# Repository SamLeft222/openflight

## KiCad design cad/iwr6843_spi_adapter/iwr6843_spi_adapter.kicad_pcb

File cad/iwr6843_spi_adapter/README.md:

# IWR6843LEVM → Raspberry Pi 5 SPI adapter

Small 2-layer board (34.0 × 25.9 mm) that plugs into the IWR6843LEVM's 60-pin
**J1** (MMWAVEICBOOST) connector and brings the radar's SPI-A port out to a
0.1" header for jumper wires to the Pi 5. The goal is to move the ~733 KB
wide-profile dump over SPI (~0.6 s at 10 MHz) instead of the ~1 Mbaud CP2105
UART (~7 s).

> **Status: rev A, not yet built or tested.** ERC, DRC and schematic–PCB
> parity pass. The firmware SPI path and Pi driver do not exist yet.

## What's on the board

| Ref | Part | Job |
|---|---|---|
| J1 | Samtec **QTH-030-01-L-D-A** (bottom side) | Mates the LEVM's J1 (QSH-030-01-L-D-A), 5.00 mm stack |
| J2 | 1×11 2.54 mm header (top side) | Jumpers to the Pi 5 |
| U1, U2 | SN74LVC2G34DBVR, powered by **radar 3V3** | Pi → radar: SCLK, MOSI, CS (U2 ch1 spare, input grounded) |
| U3 | SN74LVC2G34DBVR, powered by **Pi 3V3** | Radar → Pi: MISO, HOST_INTR |
| R1 | 100k to radar 3V3 | CS inactive (high) while the Pi pin is floating |
| R2–R5 | 100k to GND | No floating buffer inputs (SCLK, MOSI, MISO, INTR) |
| R6, R7 | 33 Ω | Damp ringing on the INTR/MISO jumpers |
| C1–C3 | 100 nF | Buffer decoupling (C3 is on the bottom) |

**Why buffers:** the IWR6843's digital I/O is not failsafe (TI SWRU585: do not
drive the pins without VIO present). The LVC2G34 has Ioff partial-power-down
(≤10 µA leakage at VCC = 0), so whichever side loses power, its buffer goes
inert and nothing back-feeds the unpowered chip.

## Before ordering (can't be checked in software)

1. **Mating orientation.** The footprint assumes QTH pin *n* mates LEVM J1
   (QSH) pin *n*, with the −A alignment pins on the row-01 side (per the
   Samtec land pattern). Print `fab/gerbers/*B_Cu*` at 1:1, or check a
   Samtec mated-pair drawing, and confirm pin 1 against the LEVM's J1
   silkscreen.
2. **Clearance behind the LEVM.** The adapter sits 5 mm under the LEVM's
   bottom side. The only bottom-side parts are J1, C3 (0.9 mm) and **J2's
   pin tails, which must be trimmed flush (≤1 mm)** so they can't touch the
   LEVM's bottom components (J6 is nearby).

## Ordering and assembly (PCBWay turnkey)

Run `./export_fab.sh` (regenerates, runs ERC/DRC, and exports into `fab/`):

| Upload | File |
|---|---|
| Gerbers + drills | `fab/iwr6843_spi_adapter-gerbers.zip` |
| BOM (PCBWay columns, MPNs) | `fab/pcbway_bom.csv` |
| Centroid / CPL | `fab/pcbway_cpl.csv` (origin = board lower-left, J2 excluded) |
| Assembly drawings | `fab/assembly/assembly_top.pdf`, `fab/assembly/assembly_bottom_mirrored.pdf` |

PCB options: 2 layers, FR-4, 1.6 mm, 1 oz, **ENIG** (flat pads for the
0.5 mm-pitch J1; HASL is too uneven), min track/spacing 5/5 mil, min hole
0.3 mm, tented vias, any mask colour.

Assembly: turnkey, **both sides** (J1 and C3 on the bottom, the rest on top).
J2 is not in the BOM or CPL. Solder it yourself and trim the tails flush.
Notes to include with the order:

> J1 (Samtec QTH-030-01-L-D-A) is on the BOTTOM side; its -A alignment pins go
> into the two 1.02 mm NPTH holes; pin 1 is marked on the bottom assembly
> drawing. U1-U3 pin 1 per the silkscreen dot. J2 (1x11 header) is NOT
> assembled. Please send placement confirmation images before production.

## LEVM setup

* Set switch **S1.4 OFF**. This routes SPI-A through the on-board TS3A5018
  mux to J1 instead of the CAN transceivers (PROC116A sheet 13). OpenFlight
  does not use CAN. TI's "functional mode" table leaves S1.4 ON; that is
  the only change.
* Keep powering the LEVM over USB as today. Do not connect J1 pin 2 (5V).

## Pi 5 wiring (jumpers ≤15 cm, cable-tie each signal to its GND)

| Adapter J2 | Signal | Pi 5 pin |
|---|---|---|
| 1 | 3V3 (powers U3) | 1 |
| 2, 4, 6, 8, 10 | GND | 6, 9, 14, 20, 25 |
| 3 | HOST_INTR (data ready) | 22 (GPIO25) |
| 5 | MISO | 21 (GPIO9) |
| 7 | MOSI | 19 (GPIO10) |
| 9 | SCLK | 23 (GPIO11) |
| 11 | CS | 24 (GPIO8 / CE0) |

None of these clash with the OPS243 UART wiring (Pi pins 2/4, 6, 8, 10, 11).
Enable SPI with `dtparam=spi=on`. Start at ≤10 MHz on jumpers.

## First power-up checks

1. Adapter only, unplugged from the LEVM: continuity between J2 even pins and
   J1 GND. No short between Pi 3V3, radar 3V3 and GND.
2. Plugged in, **everything off**: beep from J1-side nets to the LEVM's 0 Ω
   links: CS → R7, SCLK → R9, MOSI → R11, MISO → R12, INTR → R10
   (PROC116A sheet 8). This confirms the mating orientation.
3. Power the LEVM only: radar 3V3 is present at C1/C2 and U3 stays unpowered.
   Then the Pi only, then both.

## Sources

| Fact | Source |
|---|---|
| J1 pins 19/21/23/25 = SPI CS/CLK/MOSI/MISO, 16 = HOST_INTR, 4/6 = 3V3, even 20–50 = GND | TI PROC116A schematic, sheets 5, 8, 13 |
| VIOIN = 3.3 V, SPI-A behind TS3A5018, S1.4 selects SPI/CAN | PROC116A sheets 5 and 13; SWRU585 table 5-1 |
| J1 = QSH-030-01-L-D-A | PROC116A BOM |
| QTH land pattern, 5.00 mm mated height | Samtec QTH footprint Rev D, QTH print table 1 |
| LVC2G34 pinout, Ioff, DBV0006A land pattern | TI SN74LVC2G34 datasheet |

## Regenerating

Everything is generated from `generate.py` (schematic, footprints, project)
and `build_pcb.py` (placement, routing, pours). `NETS`/`PARTS` are the single
source of truth for both. Edit those, never the KiCad files.

```bash
K=/Applications/KiCad/KiCad.app/Contents
$K/Frameworks/Python.framework/Versions/Current/bin/python3 generate.py
$K/MacOS/kicad-cli sch erc --severity-all iwr6843_spi_adapter.kicad_sch
$K/MacOS/kicad-cli pcb drc --schematic-parity --refill-zones --severity-all iwr6843_spi_adapter.kicad_pcb
```

Expect only `lib_symbol_issues` / `lib_footprint_issues` warnings if your
KiCad has no global library tables configured. They are environment notices,
not design errors.

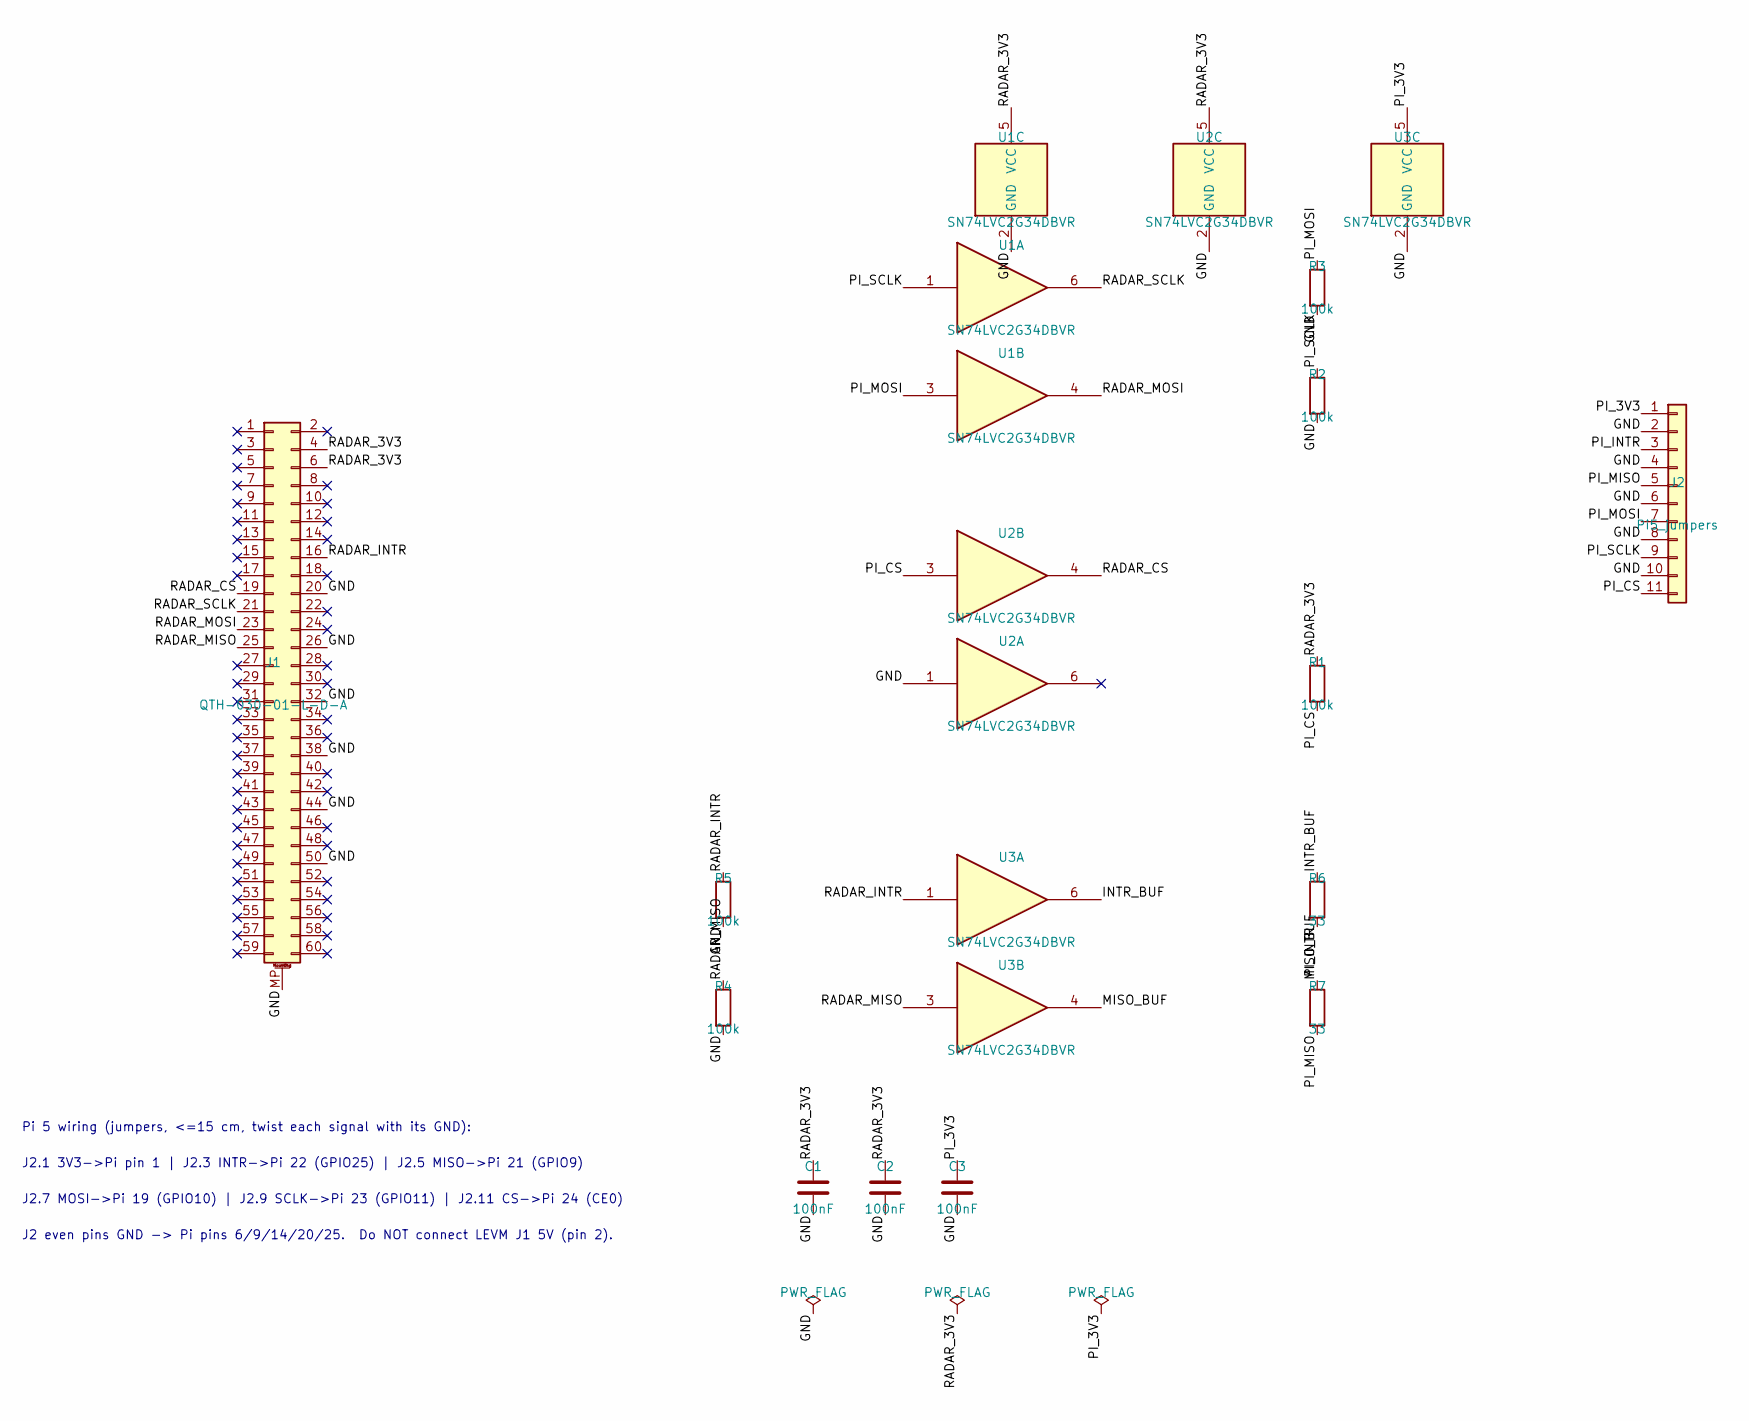
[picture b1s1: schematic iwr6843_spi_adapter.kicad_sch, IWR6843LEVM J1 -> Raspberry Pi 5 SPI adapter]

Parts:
C1, C2, C3: 100nF; C_0603_1608Metric; MPN CL10B104KB8NNNC
J1: QTH-030-01-L-D-A; Samtec_QTH-030-01-L-D-A; MPN QTH-030-01-L-D-A
J2: Pi5_jumpers; PinHeader_1x11_P2.54mm_Vertical
R1, R2, R3, R4, R5: 100k; R_0603_1608Metric; MPN RC0603FR-07100KL
R6, R7: 33; R_0603_1608Metric; MPN RC0603FR-0733RL
U1, U2, U3: SN74LVC2G34DBVR; TI_DBV0006A; MPN SN74LVC2G34DBVR

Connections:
/GND: C1.2, C2.2, C3.2, J1.20, J1.26, J1.32, J1.38, J1.44, J1.50, J1.MP (MountPin), J2.2, J2.4, J2.6, J2.8, J2.10, R2.2, R3.2, R4.2, R5.2, U1.2 (GND), U2.1, U2.2 (GND), U3.2 (GND)
/INTR_BUF: R6.1, U3.6
/MISO_BUF: R7.1, U3.4
/PI_3V3: C3.1, J2.1, U3.5 (VCC)
/PI_CS: J2.11, R1.2, U2.3
/PI_INTR: J2.3, R6.2
/PI_MISO: J2.5, R7.2
/PI_MOSI: J2.7, R3.1, U1.3
/PI_SCLK: J2.9, R2.1, U1.1
/RADAR_3V3: C1.1, C2.1, J1.4, J1.6, R1.1, U1.5 (VCC), U2.5 (VCC)
/RADAR_CS: J1.19, U2.4
/RADAR_INTR: J1.16, R5.1, U3.1
/RADAR_MISO: J1.25, R4.1, U3.3
/RADAR_MOSI: J1.23, U1.4
/RADAR_SCLK: J1.21, U1.6

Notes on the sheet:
Pi 5 wiring (jumpers, <=15 cm, twist each signal with its GND):
J2.1 3V3->Pi pin 1 | J2.3 INTR->Pi 22 (GPIO25) | J2.5 MISO->Pi 21 (GPIO9)
J2.7 MOSI->Pi 19 (GPIO10) | J2.9 SCLK->Pi 23 (GPIO11) | J2.11 CS->Pi 24 (CE0)
J2 even pins GND -> Pi pins 6/9/14/20/25. Do NOT connect LEVM J1 5V (pin 2).

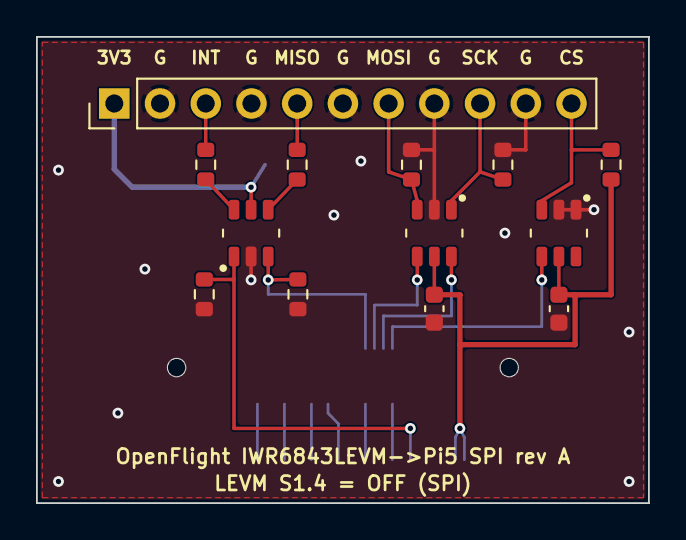
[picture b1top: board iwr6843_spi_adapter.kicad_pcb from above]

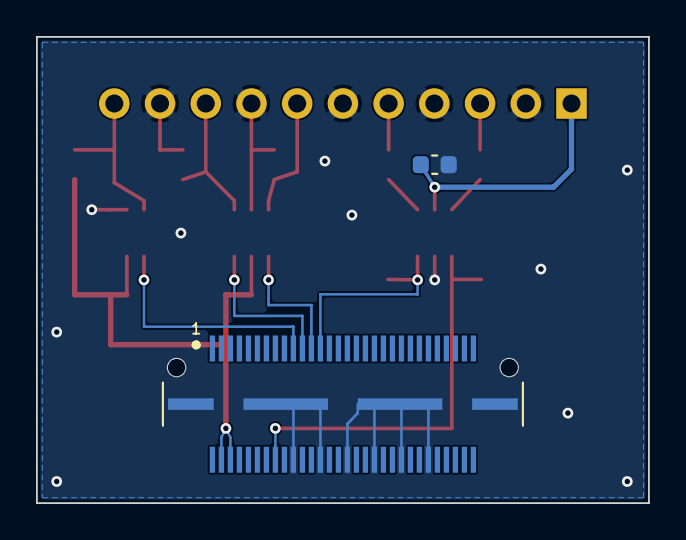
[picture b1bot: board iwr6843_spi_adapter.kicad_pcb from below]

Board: 2 copper layers, 34.0 x 25.9 mm, 15 parts (2 on the bottom side), 15 nets.

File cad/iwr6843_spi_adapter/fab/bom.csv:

"Designator","Value","Footprint","MPN","Qty"
"C1-C3","100nF","Capacitor_SMD:C_0603_1608Metric","CL10B104KB8NNNC","3"
"J1","QTH-030-01-L-D-A","openflight_adapter:Samtec_QTH-030-01-L-D-A","QTH-030-01-L-D-A","1"
"J2","Pi5_jumpers","Connector_PinHeader_2.54mm:PinHeader_1x11_P2.54mm_Vertical","","1"
"R1-R5","100k","Resistor_SMD:R_0603_1608Metric","RC0603FR-07100KL","5"
"R6,R7","33","Resistor_SMD:R_0603_1608Metric","RC0603FR-0733RL","2"
"U1-U3","SN74LVC2G34DBVR","openflight_adapter:TI_DBV0006A","SN74LVC2G34DBVR","3"
